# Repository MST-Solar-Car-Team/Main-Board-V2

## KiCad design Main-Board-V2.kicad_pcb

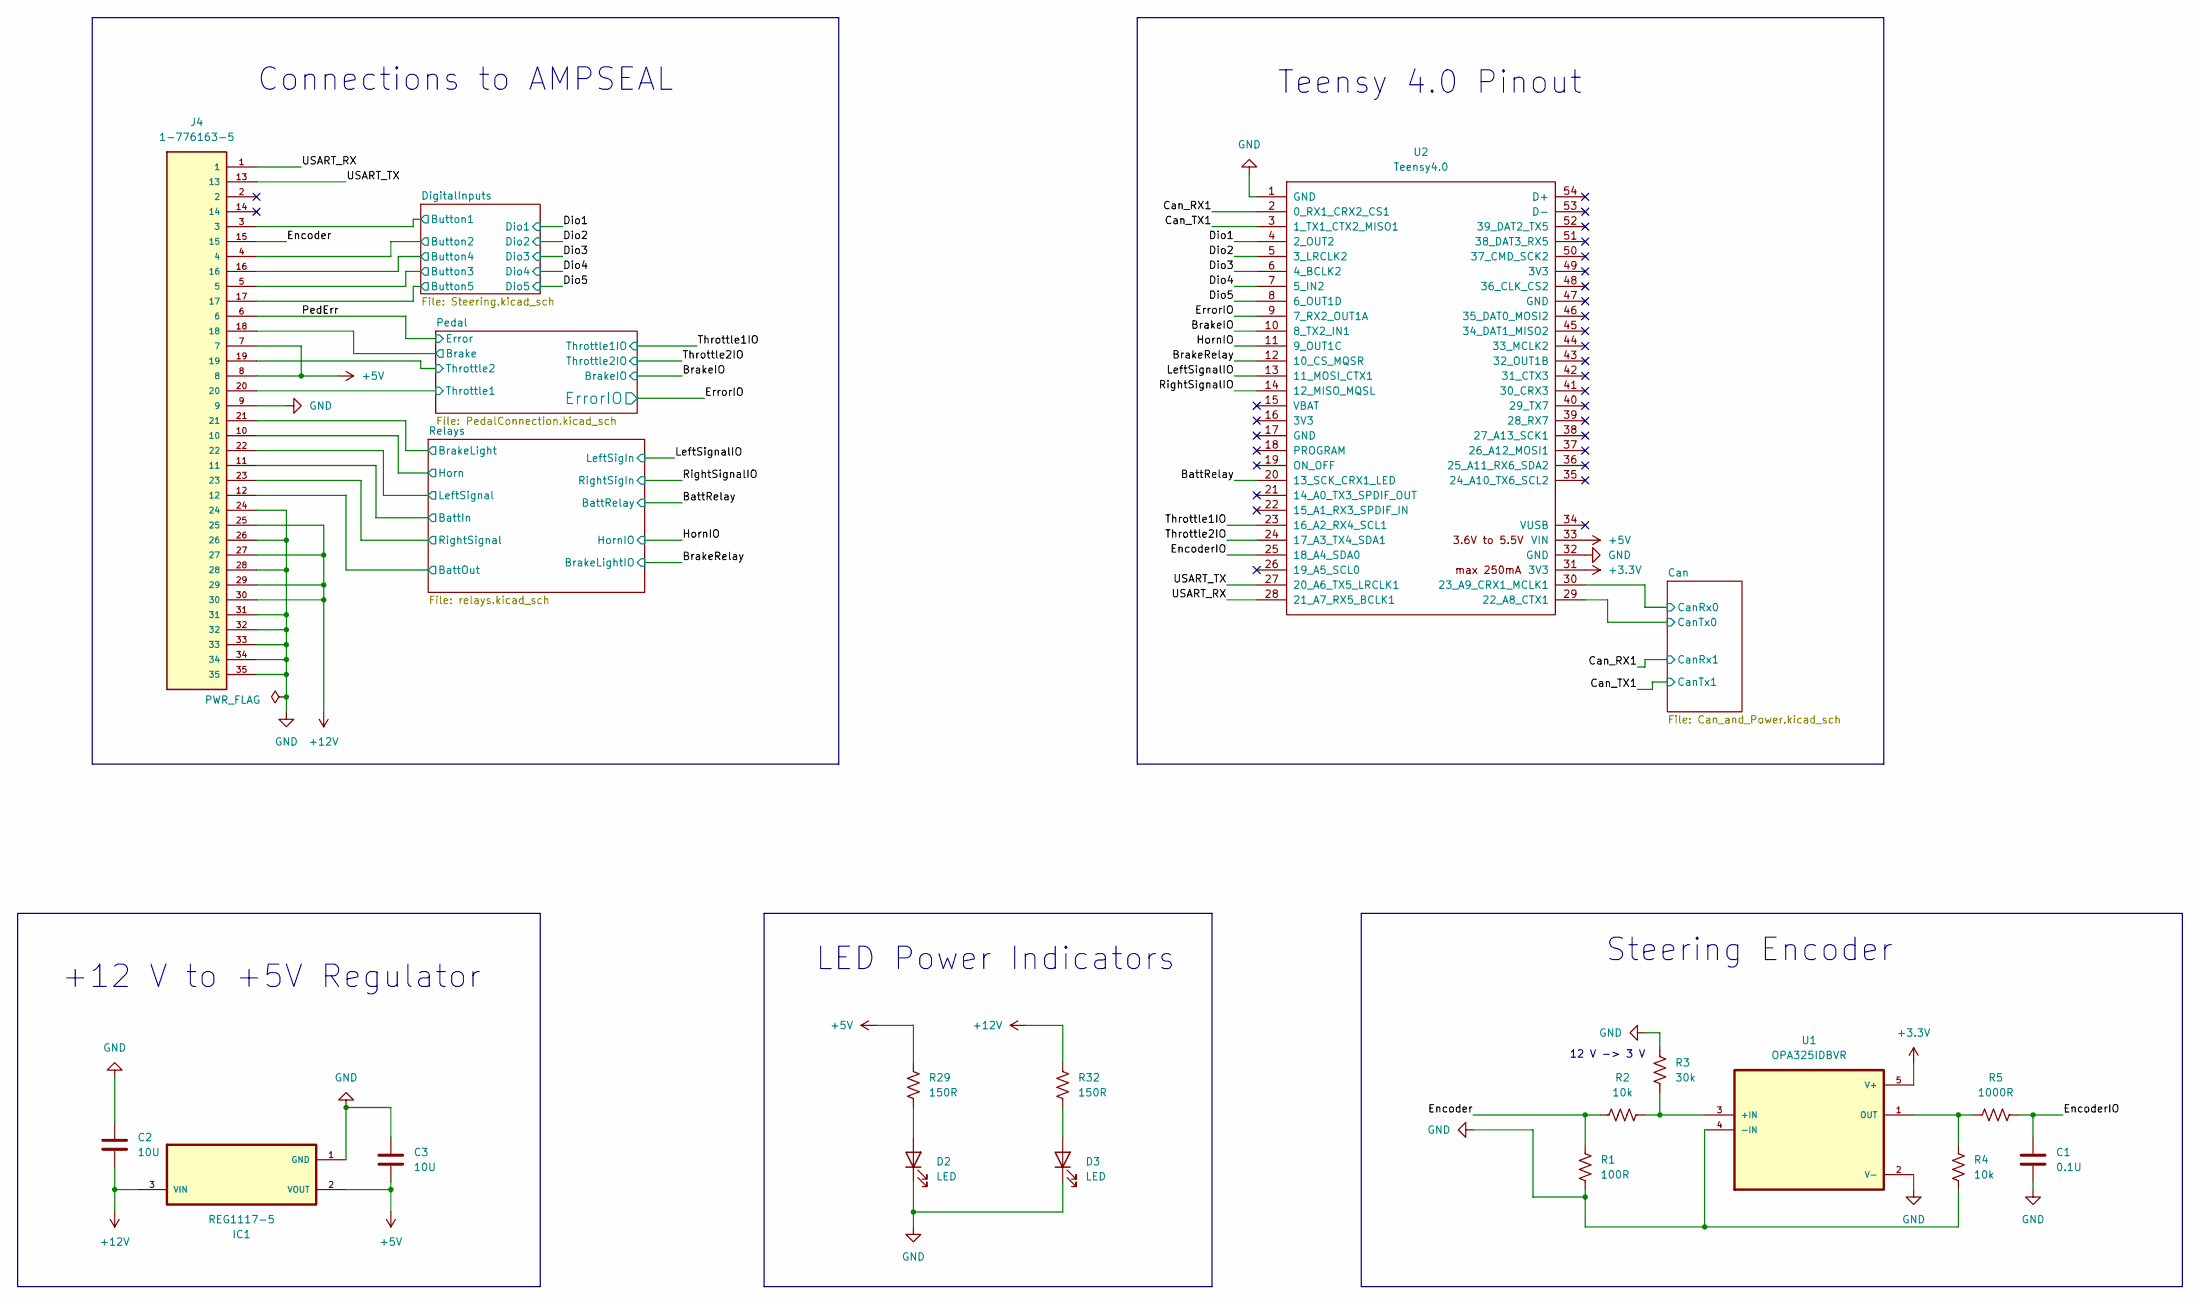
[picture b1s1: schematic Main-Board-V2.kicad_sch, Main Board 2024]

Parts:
C1: 0.1U; C_0805_2012Metric
C2, C3: 10U; C_0805_2012Metric
D2, D3: LED; LED_0805_2012Metric
IC1: REG1117-5; SOT230P700X180-4N
J4: 1-776163-5; TE_776163-5
R1: 100R; R_0805_2012Metric
R2, R4: 10k; R_0805_2012Metric
R3: 30k; R_0805_2012Metric
R5: 1000R; R_0805_2012Metric
R29, R32: 150R; R_0805_2012Metric
U1: OPA325IDBVR; SOT95P280X145-5N
U2: Teensy4.0; Teensy40_SMT

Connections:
+3.3V: U1.5 (V+), U2.31 (3V3); also elsewhere on the board
+5V: C3.2, IC1.2 (VOUT), J4.7, J4.8, R29.1, U2.33 (VIN); also elsewhere on the board
+12V: C2.2, IC1.3 (VIN), J4.25, J4.27, J4.29, J4.30, R32.1; also elsewhere on the board
/BattRelay: U2.20 (13_SCK_CRX1_LED); also elsewhere on the board
/BrakeIO: U2.10 (8_TX2_IN1); also elsewhere on the board
/BrakeRelay: U2.12 (10_CS_MQSR); also elsewhere on the board
/Can/CanRx0: U2.30 (23_A9_CRX1_MCLK1); also elsewhere on the board
/Can/CanTx0: U2.29 (22_A8_CTX1); also elsewhere on the board
/Can_RX1: U2.2 (0_RX1_CRX2_CS1); also elsewhere on the board
/Can_TX1: U2.3 (1_TX1_CTX2_MISO1); also elsewhere on the board
/DigitalInputs/Button1: J4.3; also elsewhere on the board
/DigitalInputs/Button2: J4.4; also elsewhere on the board
/DigitalInputs/Button3: J4.5; also elsewhere on the board
/DigitalInputs/Button4: J4.16; also elsewhere on the board
/DigitalInputs/Button5: J4.17; also elsewhere on the board
/Dio1: U2.4 (2_OUT2); also elsewhere on the board
/Dio2: U2.5 (3_LRCLK2); also elsewhere on the board
/Dio3: U2.6 (4_BCLK2); also elsewhere on the board
/Dio4: U2.7 (5_IN2); also elsewhere on the board
/Dio5: U2.8 (6_OUT1D); also elsewhere on the board
/Encoder: J4.15, R1.1, R2.1
/EncoderIO: C1.1, R5.2, U2.25 (18_A4_SDA0)
/ErrorIO: U2.9 (7_RX2_OUT1A); also elsewhere on the board
/HornIO: U2.11 (9_OUT1C); also elsewhere on the board
/LeftSignalIO: U2.13 (11_MOSI_CTX1); also elsewhere on the board
/PedErr: J4.6; also elsewhere on the board
/Pedal/Brake: J4.18; also elsewhere on the board
/Pedal/Throttle1: J4.20; also elsewhere on the board
/Pedal/Throttle2: J4.19; also elsewhere on the board
/Relays/BattIn: J4.11; also elsewhere on the board
/Relays/BattOut: J4.12; also elsewhere on the board
/Relays/BrakeLight: J4.21; also elsewhere on the board
/Relays/Horn: J4.10; also elsewhere on the board
/Relays/LeftSignal: J4.22; also elsewhere on the board
/Relays/RightSignal: J4.23; also elsewhere on the board
/RightSignalIO: U2.14 (12_MISO_MQSL); also elsewhere on the board
/Throttle1IO: U2.23 (16_A2_RX4_SCL1); also elsewhere on the board
/Throttle2IO: U2.24 (17_A3_TX4_SDA1); also elsewhere on the board
/USART_RX: J4.1, U2.28 (21_A7_RX5_BCLK1)
/USART_TX: J4.13, U2.27 (20_A6_TX5_LRCLK1)
GND: C1.2, C2.1, C3.1, D2.1 (K), D3.1 (K), IC1.1 (GND), J4.9, J4.24, J4.26, J4.28, J4.31, J4.32, J4.33, J4.34, J4.35, R1.2, R3.1, R4.1, U1.2 (V-), U1.4 (-IN), U2.1 (GND), U2.32 (GND); also elsewhere on the board
unnamed: D2.2 (A), R29.2
unnamed: D3.2 (A), R32.2
unnamed: R2.2, R3.2, U1.3 (+IN)
unnamed: R4.2, R5.1, U1.1 (OUT)

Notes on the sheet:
12 V -> 3 V
LED Power Indicators
Teensy 4.0 Pinout
Steering Encoder
+12 V to +5V Regulator
Connections to AMPSEAL

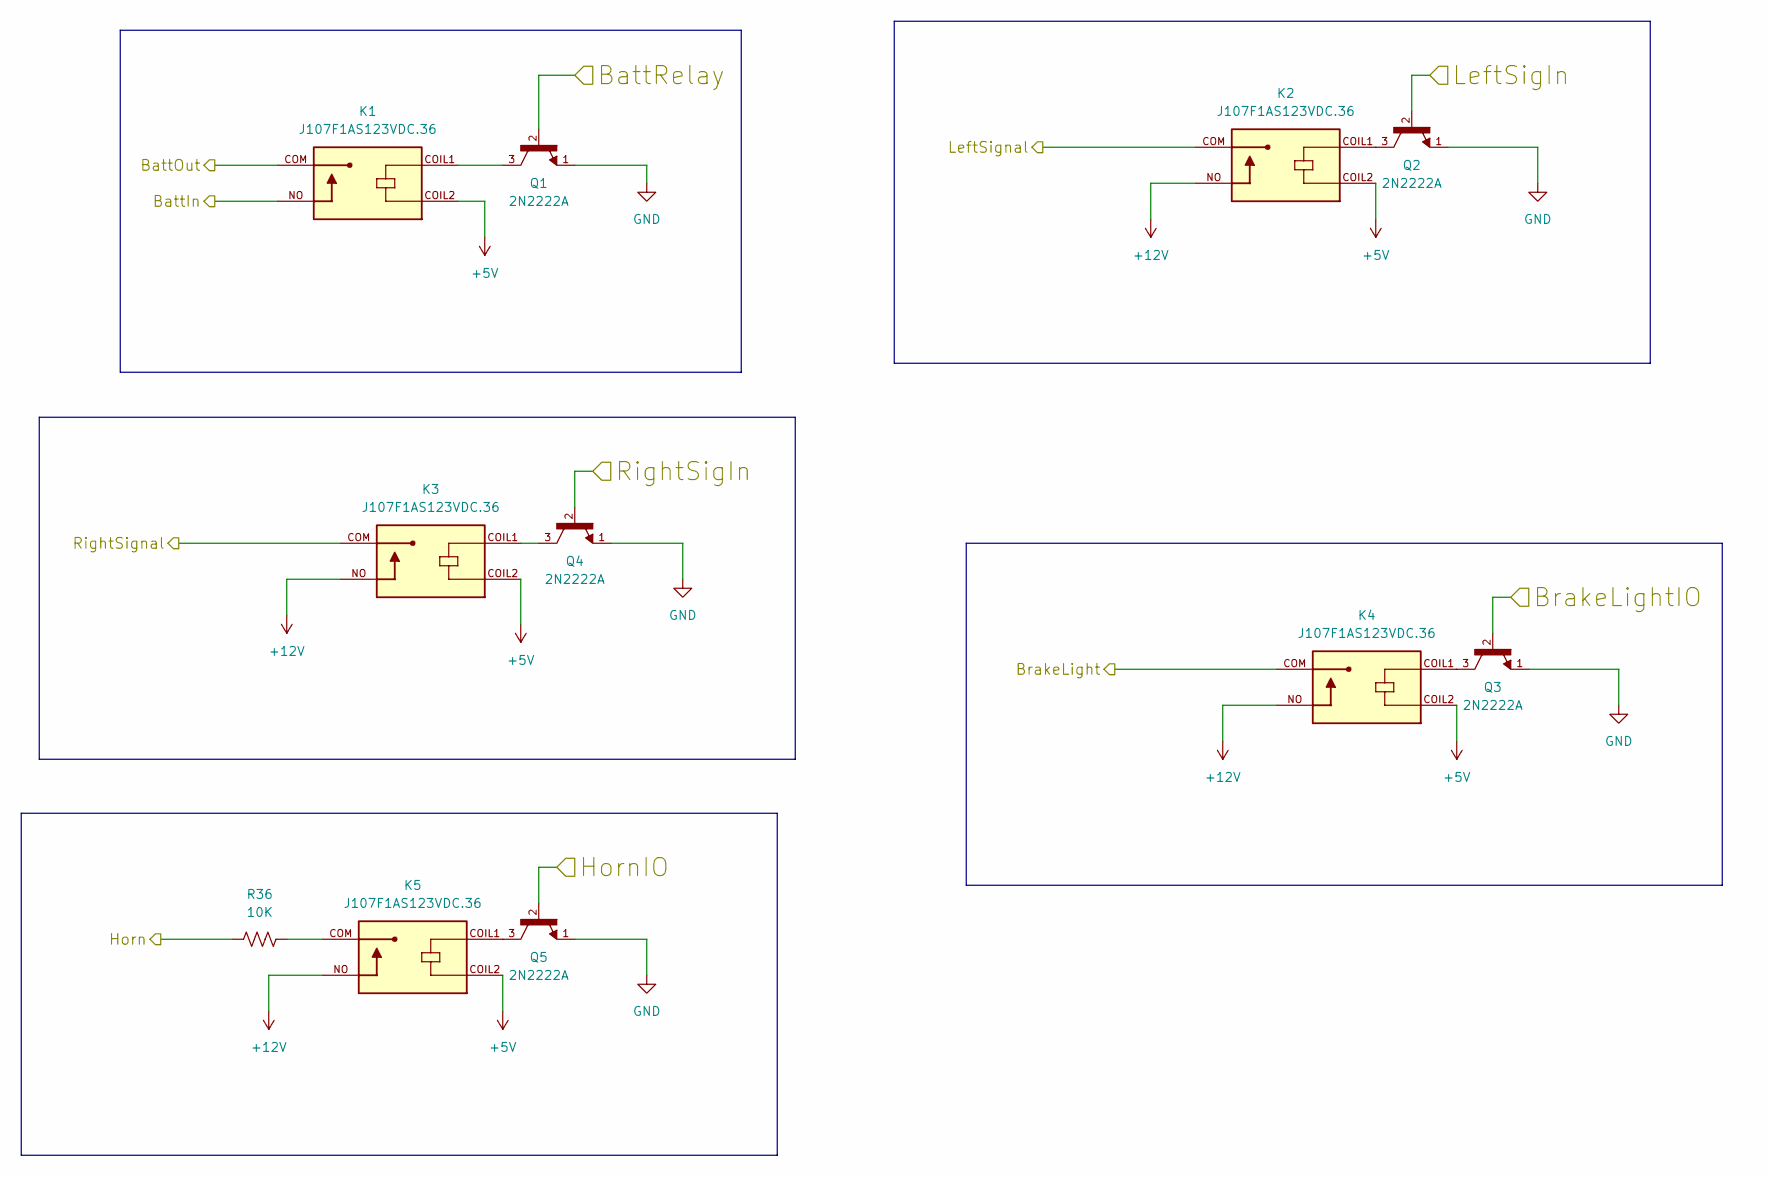
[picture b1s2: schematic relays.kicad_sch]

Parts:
K1, K2, K3, K4, K5: J107F1AS123VDC.36; RELAY_J107F1AS123VDC.36; PARTREV B
Q1, Q2, Q3, Q4, Q5: 2N2222A; TO92254P470H750-3; PARTREV N/A
R36: 10K; R_0805_2012Metric

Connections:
+5V: K1.COIL2, K2.COIL2, K3.COIL2, K4.COIL2, K5.COIL2; also elsewhere on the board
+12V: K2.NO, K3.NO, K4.NO, K5.NO; also elsewhere on the board
/BattRelay: Q1.2; also elsewhere on the board
/BrakeRelay: Q3.2; also elsewhere on the board
/HornIO: Q5.2; also elsewhere on the board
/LeftSignalIO: Q2.2; also elsewhere on the board
/Relays/BattIn: K1.NO; also elsewhere on the board
/Relays/BattOut: K1.COM; also elsewhere on the board
/Relays/BrakeLight: K4.COM; also elsewhere on the board
/Relays/Horn: R36.1; also elsewhere on the board
/Relays/LeftSignal: K2.COM; also elsewhere on the board
/Relays/RightSignal: K3.COM; also elsewhere on the board
/RightSignalIO: Q4.2; also elsewhere on the board
GND: Q1.1, Q2.1, Q3.1, Q4.1, Q5.1; also elsewhere on the board
unnamed: K1.COIL1, Q1.3
unnamed: K2.COIL1, Q2.3
unnamed: K3.COIL1, Q4.3
unnamed: K4.COIL1, Q3.3
unnamed: K5.COIL1, Q5.3
unnamed: K5.COM, R36.2

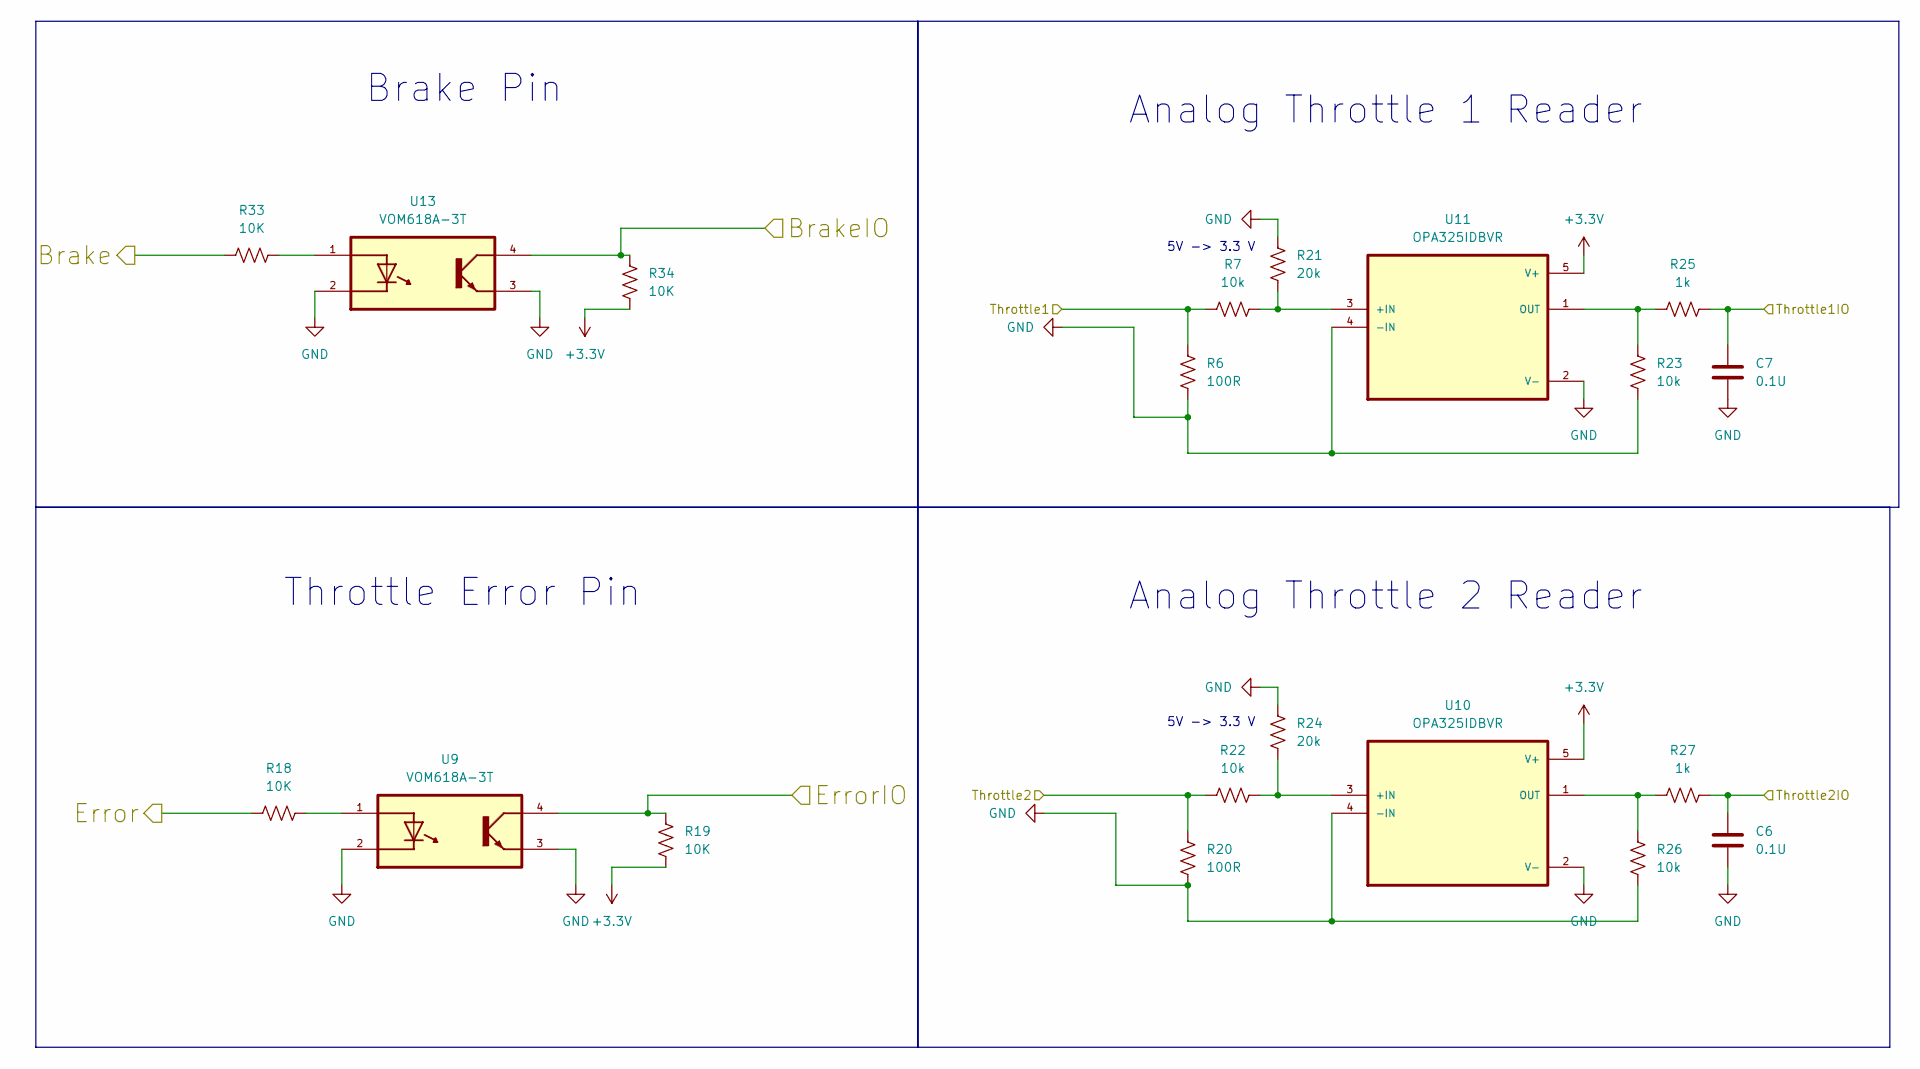
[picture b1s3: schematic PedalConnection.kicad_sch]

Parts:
C6, C7: 0.1U; C_0805_2012Metric
R6, R20: 100R; R_0805_2012Metric
R7, R22, R23, R26: 10k; R_0805_2012Metric
R18, R19, R33, R34: 10K; R_0805_2012Metric
R21, R24: 20k; R_0805_2012Metric
R25, R27: 1k; R_0805_2012Metric
U9, U13: VOM618A-3T; SOIC254P695X242-4N
U10, U11: OPA325IDBVR; SOT95P280X145-5N

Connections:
+3.3V: R19.2, R34.2, U10.5 (V+), U11.5 (V+); also elsewhere on the board
/BrakeIO: R34.1, U13.4; also elsewhere on the board
/ErrorIO: R19.1, U9.4; also elsewhere on the board
/PedErr: R18.1; also elsewhere on the board
/Pedal/Brake: R33.1; also elsewhere on the board
/Pedal/Throttle1: R6.1, R7.1; also elsewhere on the board
/Pedal/Throttle2: R20.1, R22.1; also elsewhere on the board
/Throttle1IO: C7.1, R25.2; also elsewhere on the board
/Throttle2IO: C6.1, R27.2; also elsewhere on the board
GND: C6.2, C7.2, R6.2, R20.2, R21.1, R23.1, R24.1, R26.1, U9.2, U9.3, U10.2 (V-), U10.4 (-IN), U11.2 (V-), U11.4 (-IN), U13.2, U13.3; also elsewhere on the board
unnamed: R18.2, U9.1
unnamed: R33.2, U13.1
unnamed: R22.2, R24.2, U10.3 (+IN)
unnamed: R26.2, R27.1, U10.1 (OUT)
unnamed: R7.2, R21.2, U11.3 (+IN)
unnamed: R23.2, R25.1, U11.1 (OUT)

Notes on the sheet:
Throttle Error Pin
Brake Pin
Analog Throttle 1 Reader
5V -> 3.3 V
Analog Throttle 2 Reader

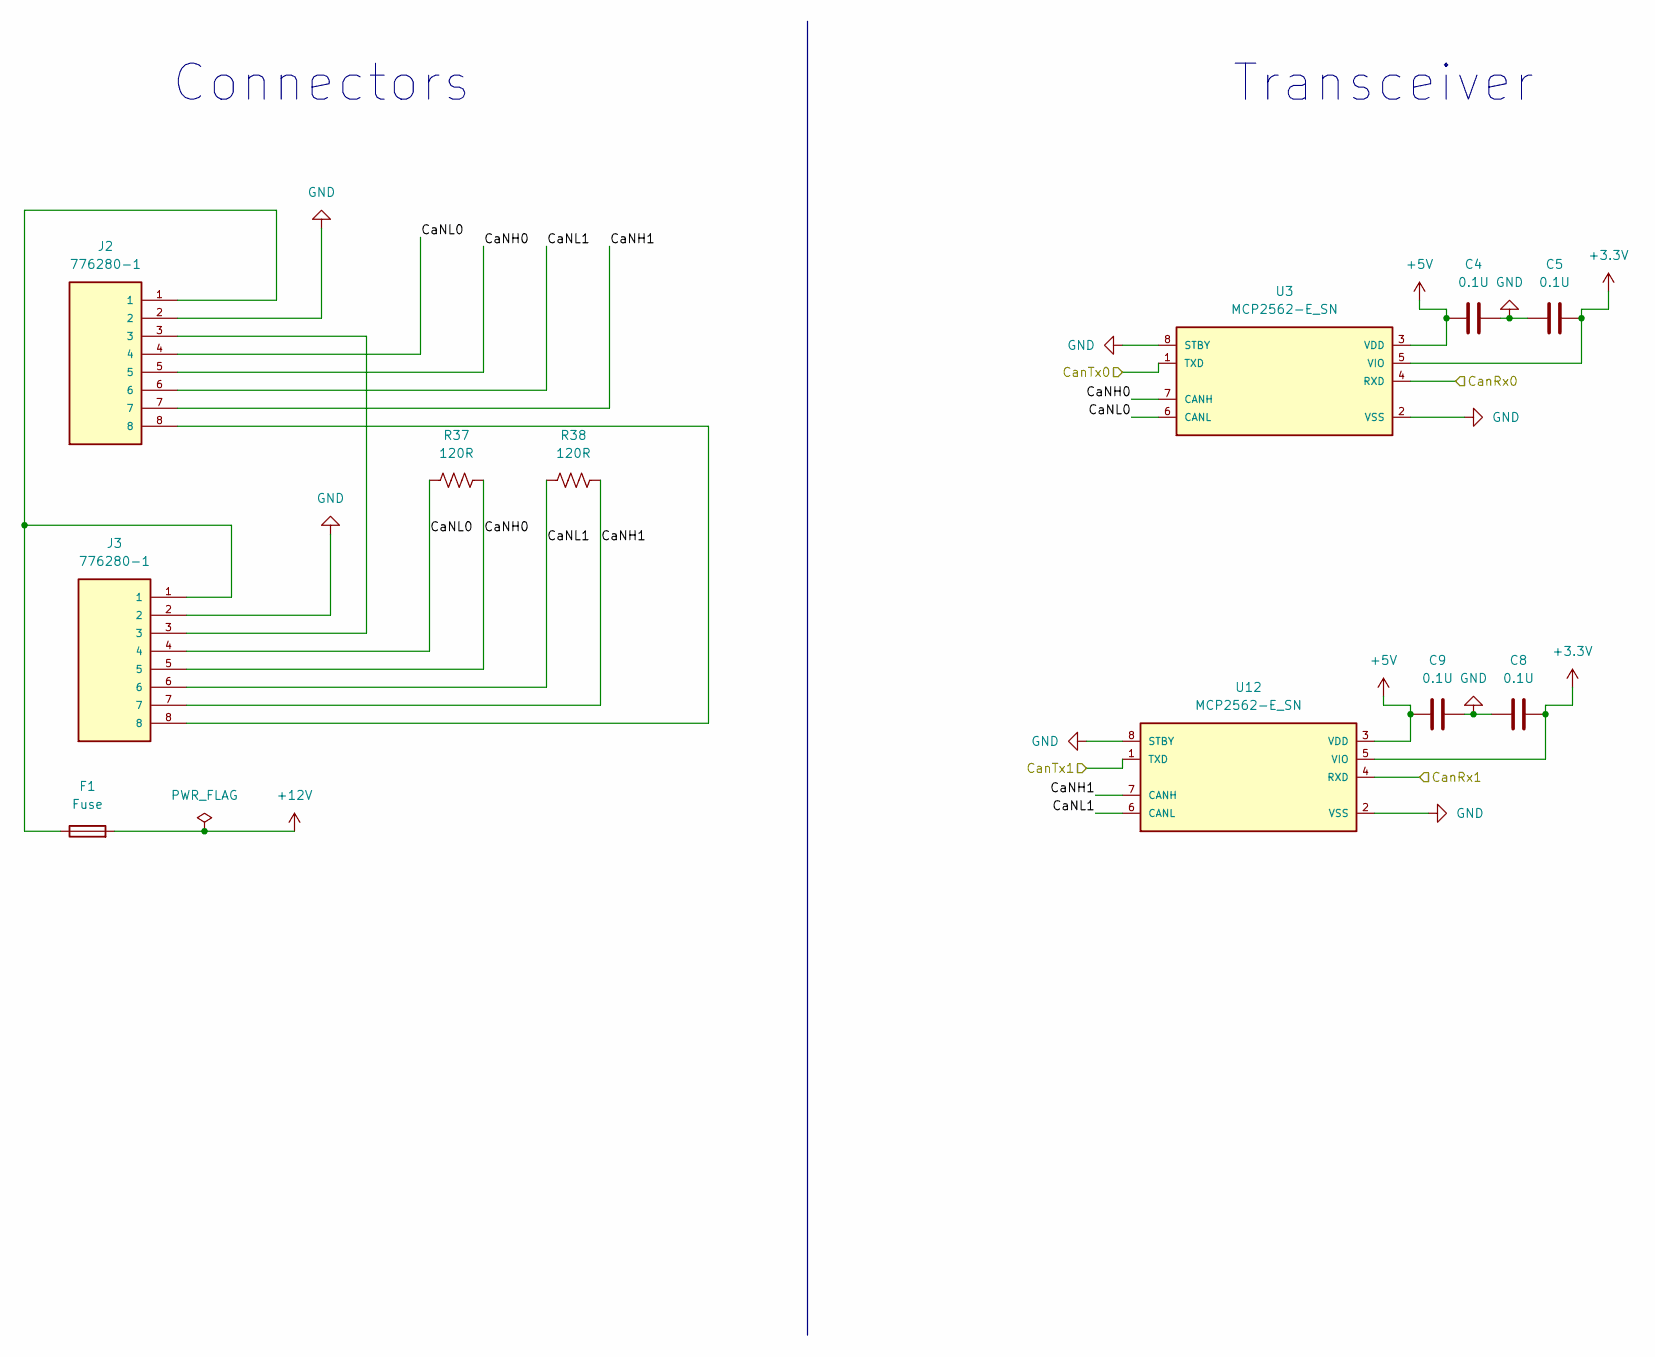
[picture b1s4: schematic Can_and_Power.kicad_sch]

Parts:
C4, C5, C8, C9: 0.1U; C_0805_2012Metric
F1: Fuse; Fuse_0805_2012Metric
J2, J3: 776280-1; TE_776280-1; PARTREV F8
R37, R38: 120R; R_0805_2012Metric
U3, U12: MCP2562-E_SN; SOIC127P600X175-8N

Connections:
+3.3V: C5.2, C8.2, U3.5 (VIO), U12.5 (VIO); also elsewhere on the board
+5V: C4.1, C9.1, U3.3 (VDD), U12.3 (VDD); also elsewhere on the board
+12V: F1.2; also elsewhere on the board
/Can/CaNH0: J2.5, J3.5, R37.2, U3.7 (CANH)
/Can/CaNH1: J2.7, J3.7, R38.2, U12.7 (CANH)
/Can/CaNL0: J2.4, J3.4, R37.1, U3.6 (CANL)
/Can/CaNL1: J2.6, J3.6, R38.1, U12.6 (CANL)
/Can/CanRx0: U3.4 (RXD); also elsewhere on the board
/Can/CanTx0: U3.1 (TXD); also elsewhere on the board
/Can_RX1: U12.4 (RXD); also elsewhere on the board
/Can_TX1: U12.1 (TXD); also elsewhere on the board
GND: C4.2, C5.1, C8.1, C9.2, J2.2, J3.2, U3.2 (VSS), U3.8 (STBY), U12.2 (VSS), U12.8 (STBY); also elsewhere on the board
unnamed: F1.1, J2.1, J3.1
unnamed: J2.3, J3.3
unnamed: J2.8, J3.8

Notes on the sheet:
Connectors
Transceiver

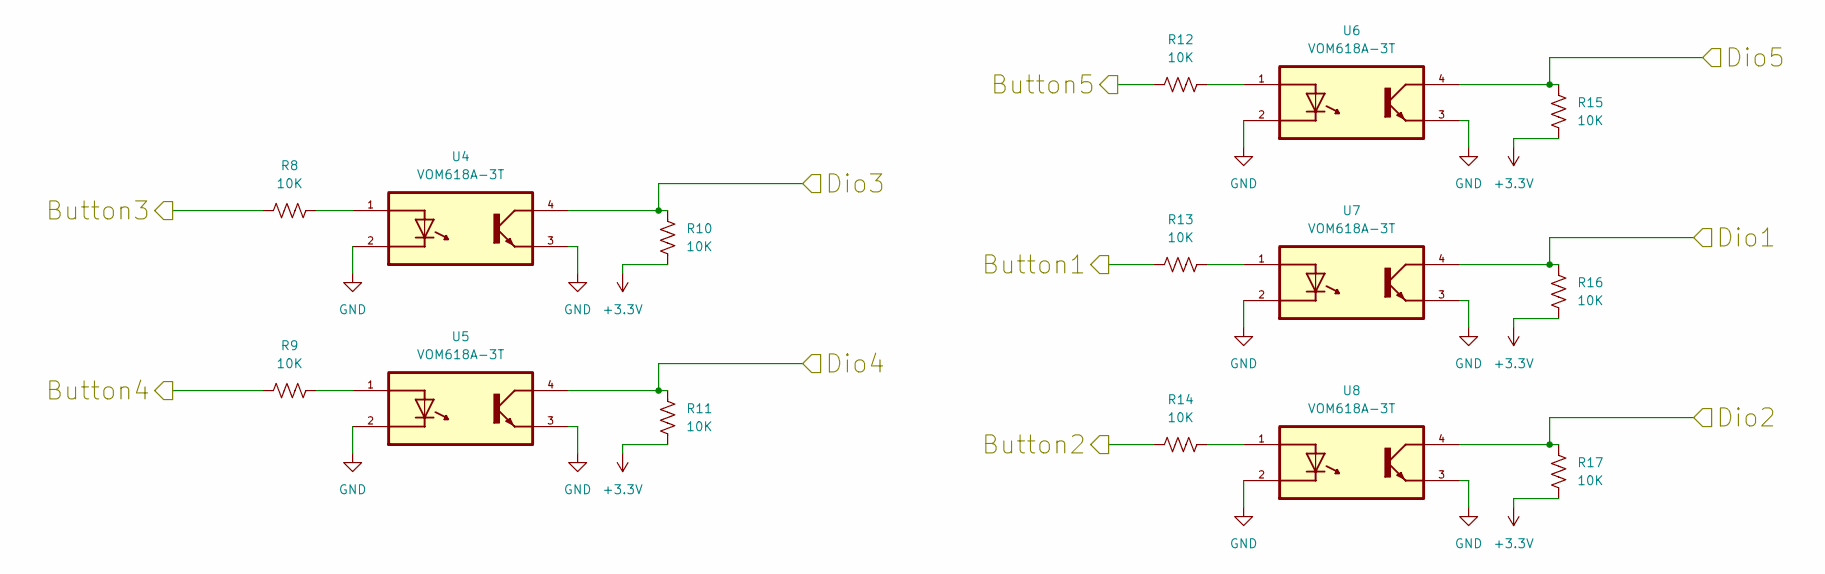
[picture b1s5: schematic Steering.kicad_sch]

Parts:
R8, R9, R10, R11, R12, R13, R14, R15, R16, R17: 10K; R_0805_2012Metric
U4, U5, U6, U7, U8: VOM618A-3T; SOIC254P695X242-4N

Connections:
+3.3V: R10.2, R11.2, R15.2, R16.2, R17.2; also elsewhere on the board
/DigitalInputs/Button1: R13.1; also elsewhere on the board
/DigitalInputs/Button2: R14.1; also elsewhere on the board
/DigitalInputs/Button3: R8.1; also elsewhere on the board
/DigitalInputs/Button4: R9.1; also elsewhere on the board
/DigitalInputs/Button5: R12.1; also elsewhere on the board
/Dio1: R16.1, U7.4; also elsewhere on the board
/Dio2: R17.1, U8.4; also elsewhere on the board
/Dio3: R10.1, U4.4; also elsewhere on the board
/Dio4: R11.1, U5.4; also elsewhere on the board
/Dio5: R15.1, U6.4; also elsewhere on the board
GND: U4.2, U4.3, U5.2, U5.3, U6.2, U6.3, U7.2, U7.3, U8.2, U8.3; also elsewhere on the board
unnamed: R8.2, U4.1
unnamed: R9.2, U5.1
unnamed: R12.2, U6.1
unnamed: R13.2, U7.1
unnamed: R14.2, U8.1

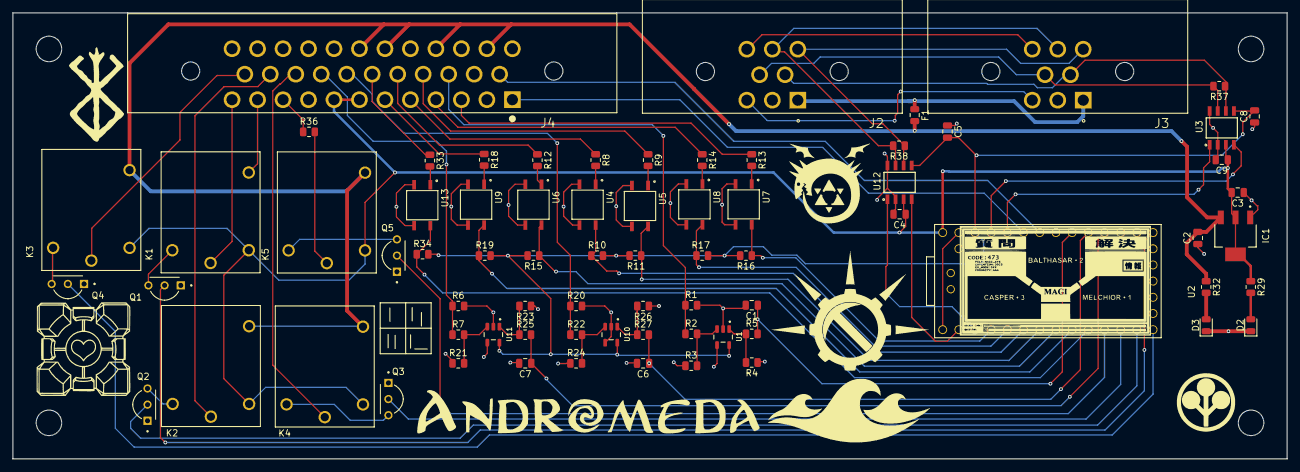
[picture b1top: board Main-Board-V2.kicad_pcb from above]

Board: 2 copper layers, 200.0 x 70.0 mm, 73 parts (0 on the bottom side), 69 nets.

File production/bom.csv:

Designator,Footprint,Quantity,Value,LCSC Part #
"C1, C4, C5, C6, C7, C8, C9",0805,7,0.1U,
"C2, C3",0805,2,10U,
"D2, D3",0805,2,LED,
F1,0805,1,Fuse,
IC1,SOT230P700X180-4N,1,REG1117-5,
"J2, J3",TE_776280-1,2,776280-1,
J4,TE_776163-5,1,1-776163-5,
"K1, K2, K3, K4, K5",RELAY_J107F1AS123VDC.36,5,J107F1AS123VDC.36,
"Q1, Q2, Q3, Q4, Q5",TO92254P470H750-3,5,2N2222A,
"R1, R20, R6",0805,3,100R,
"R10, R11, R12, R13, R14, R15, R16, R17, R18, R19, R2, R22, R23, R26, R33, R34, R36, R4, R7, R8, R9",0805,21,10K,
"R21, R24",0805,2,20k,
"R25, R27",0805,2,1k,
"R29, R32",0805,2,150R,
R3,0805,1,30k,
"R37, R38",0805,2,120R,
R5,0805,1,1000R,
"U1, U10, U11",SOT95P280X145-5N,3,OPA325IDBVR,
"U12, U3",SOIC127P600X175-8N,2,MCP2562-E_SN,
"U13, U4, U5, U6, U7, U8, U9",SOIC254P695X242-4N,7,VOM618A-3T,
U2,Teensy40_SMT,1,Teensy4.0,

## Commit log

2025-10-07 Added Can and power stuff to board
2025-10-09 Seperated into sub sheets
2025-10-14 Digital IO, Relay, and Switchbox changes
2025-10-14 Fixed Relay output to not short +12V
2025-10-14 Added Analog inputs
2025-10-15 Fixed ERC errors and warnings
2025-10-15 Added 5V to switchbox
2025-10-16 Added transistor to control relays
2025-10-17 Moved everything to 23-POS AmpSeal
2025-10-28 Final Pinout for connectors
2025-10-28 Swapped battery relay pins
2025-11-17 Idk what but it is better than before
2025-12-14 There is something different. Will fix soon, previous save is better
2025-12-18 made connector match drawing
2025-12-18 placed most components
2025-12-18 replaced CAN chip, power planes
2025-12-18 Finished routing
2025-12-18 I've been a busy boy
2025-12-20 Added silkscreen logo
2025-12-20 Moved CAN Ports to same side of board
2025-12-29 Finalized analog components. Everything is done 🙏
2025-12-31 Added fuse, switch to horizontal connecotor, redid all routing
2026-01-06 finished re-routing, only silkscreen errors left
2026-01-06 fixed silk screen
2026-01-11 added LED indicators, fixed footprints
2026-01-11 fixed 3d models
2026-01-11 exported for manufacturing
2026-04-09 idk, probably nothing
2026-04-23 redid 35 pos pinout
2026-04-23 fixed pcb excpet relays
2026-04-23 complete. Minor Tweaks
2026-04-23 removed resistors for light boards
2026-04-24 fixed mounting holes
2026-04-26 front silkscreen
2026-04-26 finished silkscreen
2026-04-26 fixed relays
